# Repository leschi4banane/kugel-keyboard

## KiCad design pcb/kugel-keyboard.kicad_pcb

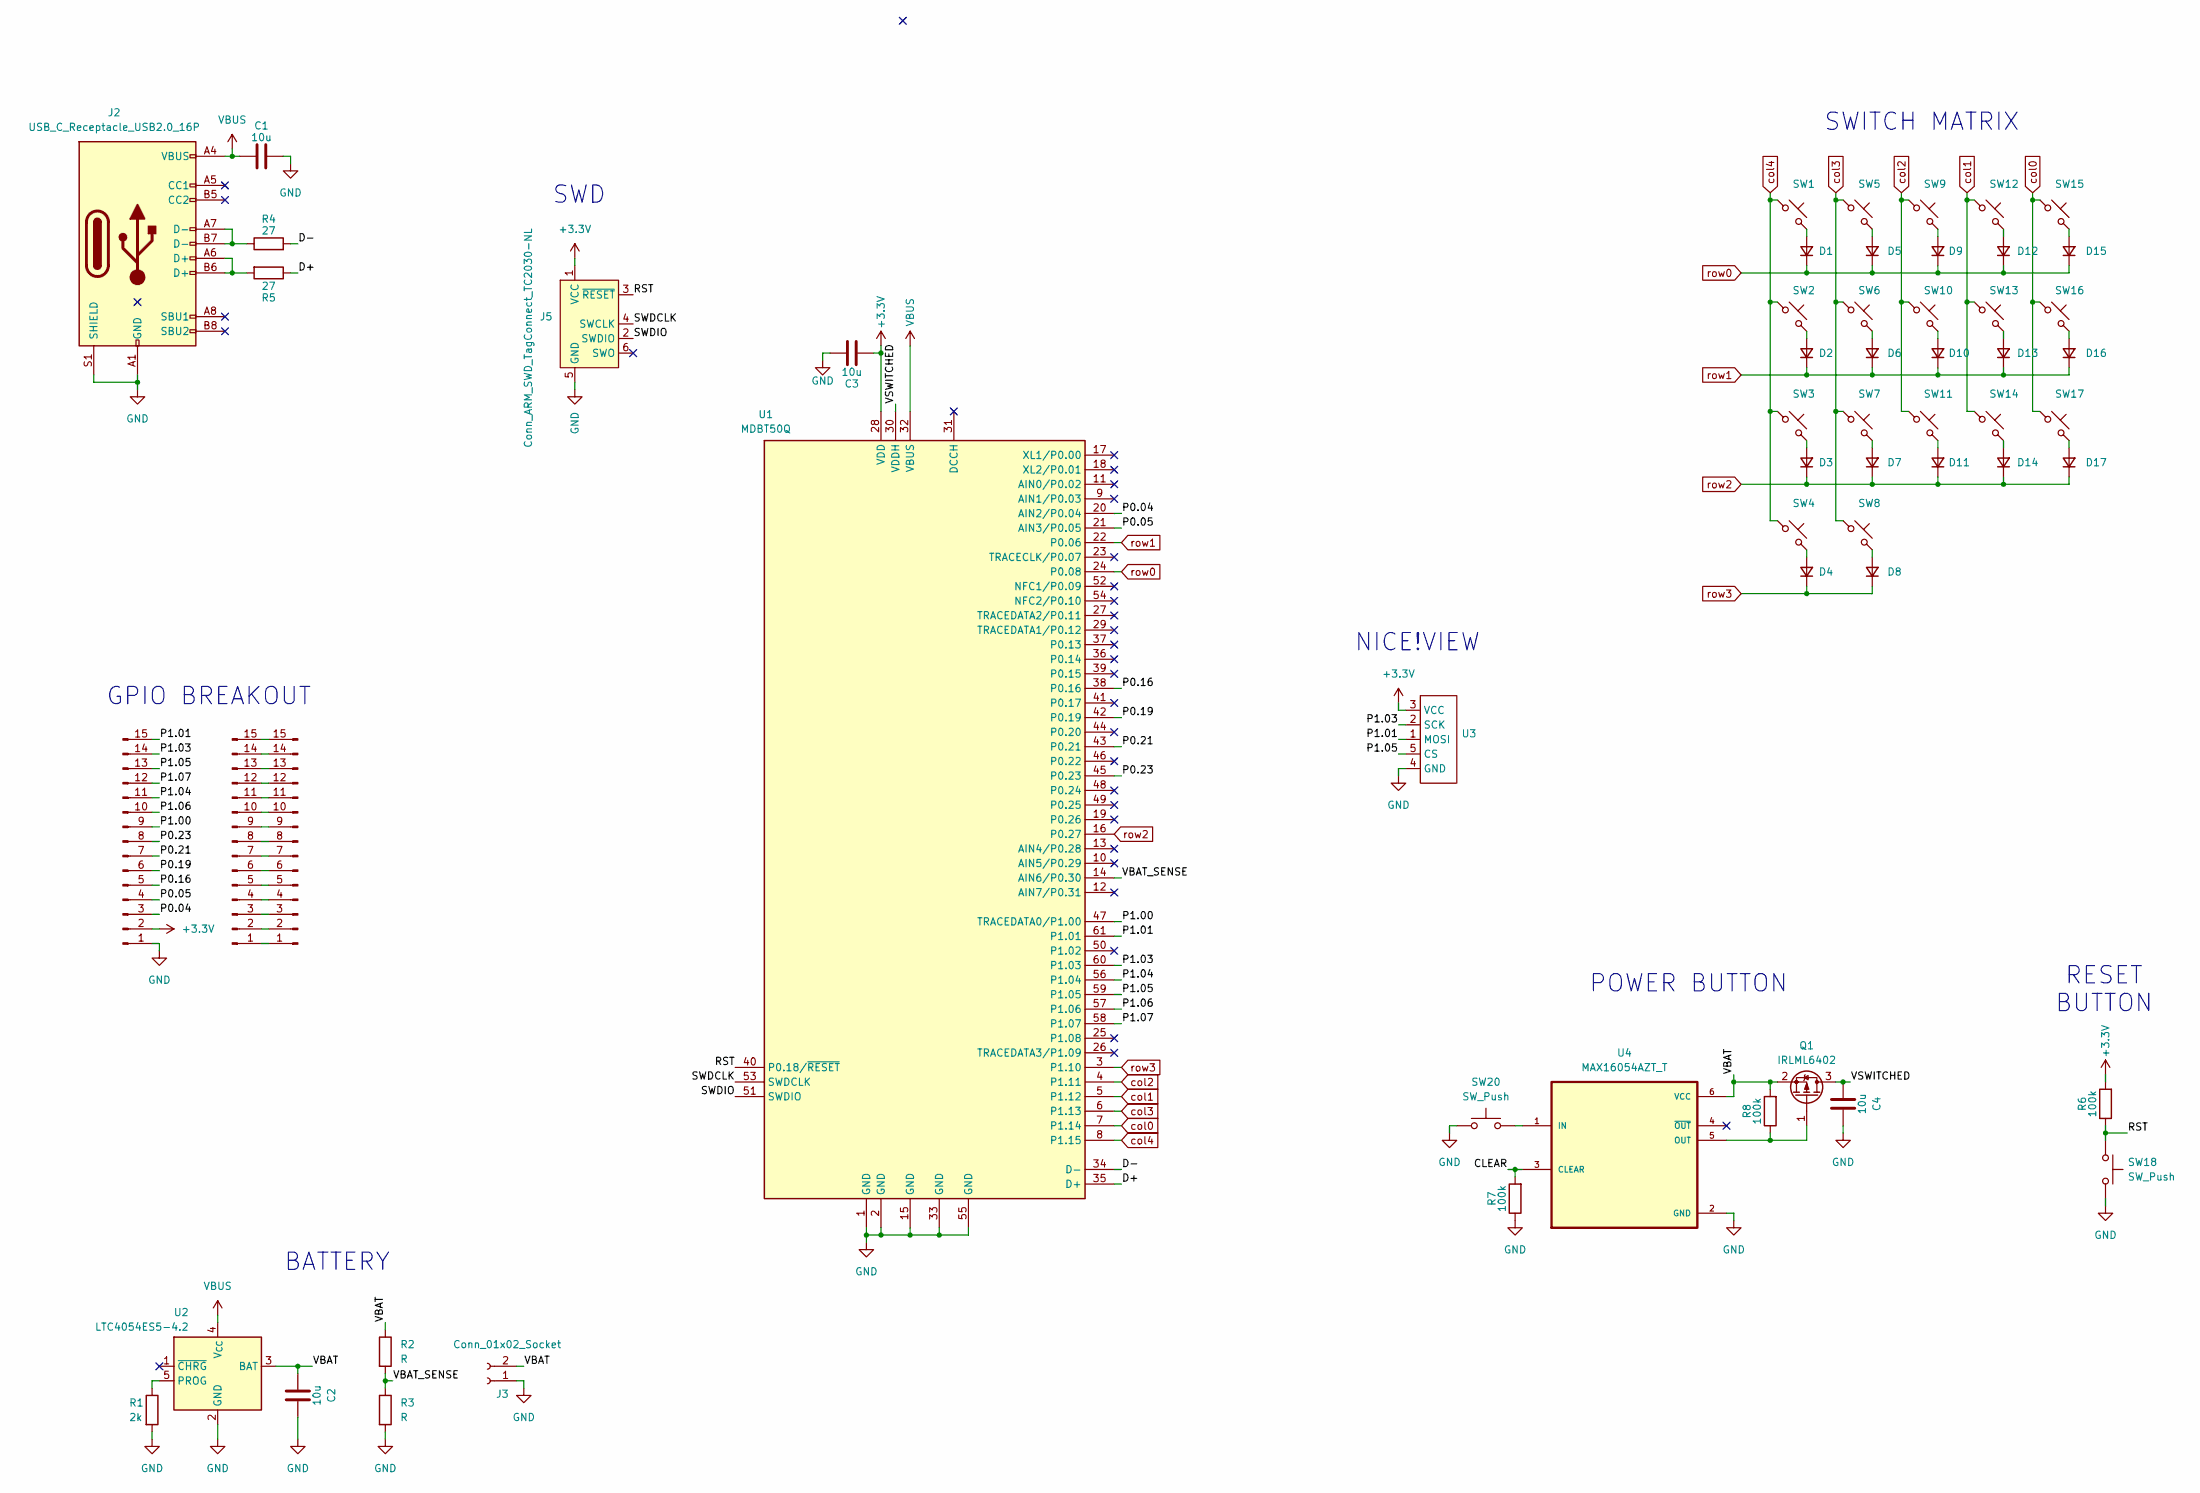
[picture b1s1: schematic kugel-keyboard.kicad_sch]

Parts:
C1, C2, C3, C4: 10u; C_0603_1608Metric_Pad1.08x0.95mm_HandSolder
D1, D2, D3, D4, D5, D6, D7, D8, D9, D10, D11, D12, D13, D14, D15, D16, D17: D_Small; Nexperia_CFP3_SOD-123W
J1, J6: Conn_01x15_Pin; Hirose_FH12-15S-0.5SH_1x15-1MP_P0.50mm_Horizontal
J2: USB_C_Receptacle_USB2.0_16P; USB_C_Receptacle_GCT_USB4105-xx-A_16P_TopMnt_Horizontal
J3: Conn_01x02_Socket; Battery_solder_pads
J4: Conn_01x15_Pin; PinHeader_1x15_P2.54mm_Vertical
J5: Conn_ARM_SWD_TagConnect_TC2030-NL; Tag-Connect_TC2030-IDC-NL_2x03_P1.27mm_Vertical
Q1: IRLML6402; SOT-23
R1: 2k; R_0603_1608Metric_Pad0.98x0.95mm_HandSolder
R2, R3: R; R_0603_1608Metric_Pad0.98x0.95mm_HandSolder
R4, R5: 27; R_0603_1608Metric_Pad0.98x0.95mm_HandSolder
R6, R7, R8: 100k; R_0603_1608Metric_Pad0.98x0.95mm_HandSolder
SW1, SW2, SW3, SW4, SW5, SW6, SW7, SW8, SW9, SW10, SW11, SW12, SW13, SW14, SW15, SW16, SW17: MX_SW_HS; Kailh_socket_PG1350
SW18, SW20: SW_Push; SW_TL6340AF160Q
U1: MDBT50Q; MDBT50Q-1MV2
U2: LTC4054ES5-4.2; TSOT-23-5
U3: nice!view
U4: MAX16054AZT_T; SOT95P275X110-6N

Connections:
+3.3V: C3.1, J5.1 (VCC), J6.2, R6.2, U1.28 (VDD), U3.3 (VCC)
/CLEAR: R7.2, U4.3 (CLEAR)
/D+: R5.1, U1.35 (D+)
/D-: R4.2, U1.34 (D-)
/P0.04: J6.3, U1.20 (AIN2/P0.04)
/P0.05: J6.4, U1.21 (AIN3/P0.05)
/P0.16: J6.5, U1.38 (P0.16)
/P0.19: J6.6, U1.42 (P0.19)
/P0.21: J6.7, U1.43 (P0.21)
/P0.23: J6.8, U1.45 (P0.23)
/P1.00: J6.9, U1.47 (TRACEDATA0/P1.00)
/P1.01: J6.15, U1.61 (P1.01), U3.1 (MOSI)
/P1.03: J6.14, U1.60 (P1.03), U3.2 (SCK)
/P1.04: J6.11, U1.56 (P1.04)
/P1.05: J6.13, U1.59 (P1.05), U3.5 (CS)
/P1.06: J6.10, U1.57 (P1.06)
/P1.07: J6.12, U1.58 (P1.07)
/RST: J5.3 (~RESET), R6.1, SW18.1, U1.40 (P0.18/~RESET)
/SWDCLK: J5.4 (SWCLK), U1.53 (SWDCLK)
/SWDIO: J5.2 (SWDIO), U1.51 (SWDIO)
/VBAT: C2.1, J3.2, Q1.2 (S), R2.1, R8.2, U2.3 (BAT), U4.6 (VCC)
/VBAT_SENSE: R2.2, R3.1, U1.14 (AIN6/P0.30)
/VSWITCHED: C4.1, Q1.3 (D), U1.30 (VDDH)
GND: C1.2, C2.2, C3.2, C4.2, J2.A1 (GND), J2.A12 (GND), J2.B1 (GND), J2.B12 (GND), J2.S1 (SHIELD), J3.1, J5.5 (GND), J6.1, J6.MP, R1.2, R3.2, R7.1, SW18.2, SW20.1, U1.1 (GND), U1.2 (GND), U1.15 (GND), U1.33 (GND), U1.55 (GND), U2.2 (GND), U3.4 (GND), U4.2 (GND)
unnamed: D1.2 (A), SW1.2
unnamed: D2.2 (A), SW2.2
unnamed: D3.2 (A), SW3.2
unnamed: D4.2 (A), SW4.2
unnamed: D5.2 (A), SW5.2
unnamed: D6.2 (A), SW6.2
unnamed: D7.2 (A), SW7.2
unnamed: D8.2 (A), SW8.2
unnamed: D9.2 (A), SW9.2
unnamed: D10.2 (A), SW10.2
unnamed: D11.2 (A), SW11.2
unnamed: D12.2 (A), SW12.2
unnamed: D13.2 (A), SW13.2
unnamed: D14.2 (A), SW14.2
unnamed: D15.2 (A), SW15.2
unnamed: D16.2 (A), SW16.2
unnamed: D17.2 (A), SW17.2
unnamed: J1.1, J4.1
unnamed: J1.2, J4.2
unnamed: J1.3, J4.3
unnamed: J1.4, J4.4
unnamed: J1.5, J4.5
unnamed: J1.6, J4.6
unnamed: J1.7, J4.7
unnamed: J1.8, J4.8
unnamed: J1.9, J4.9
unnamed: J1.10, J4.10
unnamed: J1.11, J4.11
unnamed: J1.12, J4.12
unnamed: J1.13, J4.13
unnamed: J1.14, J4.14
unnamed: J1.15, J4.15
unnamed: J2.A6 (D+), J2.B6 (D+), R5.2
unnamed: J2.A7 (D-), J2.B7 (D-), R4.1
unnamed: Q1.1 (G), R8.1, U4.5 (OUT)
unnamed: R1.1, U2.5 (PROG)
unnamed: SW20.2, U4.1 (IN)
VBUS: C1.1, J2.A4 (VBUS), J2.A9 (VBUS), J2.B4 (VBUS), J2.B9 (VBUS), U1.32 (VBUS), U2.4 (V_{CC})
col0: SW15.1, SW16.1, SW17.1, U1.7 (P1.14)
col1: SW12.1, SW13.1, SW14.1, U1.5 (P1.12)
col2: SW9.1, SW10.1, SW11.1, U1.4 (P1.11)
col3: SW5.1, SW6.1, SW7.1, SW8.1, U1.6 (P1.13)
col4: SW1.1, SW2.1, SW3.1, SW4.1, U1.8 (P1.15)
row0: D1.1 (K), D5.1 (K), D9.1 (K), D12.1 (K), D15.1 (K), U1.24 (P0.08)
row1: D2.1 (K), D6.1 (K), D10.1 (K), D13.1 (K), D16.1 (K), U1.22 (P0.06)
row2: D3.1 (K), D7.1 (K), D11.1 (K), D14.1 (K), D17.1 (K), U1.16 (P0.27)
row3: D4.1 (K), D8.1 (K), U1.3 (P1.10)

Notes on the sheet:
RESET BUTTON
GPIO BREAKOUT
NICE!VIEW
POWER BUTTON
SWITCH MATRIX
SWD
BATTERY

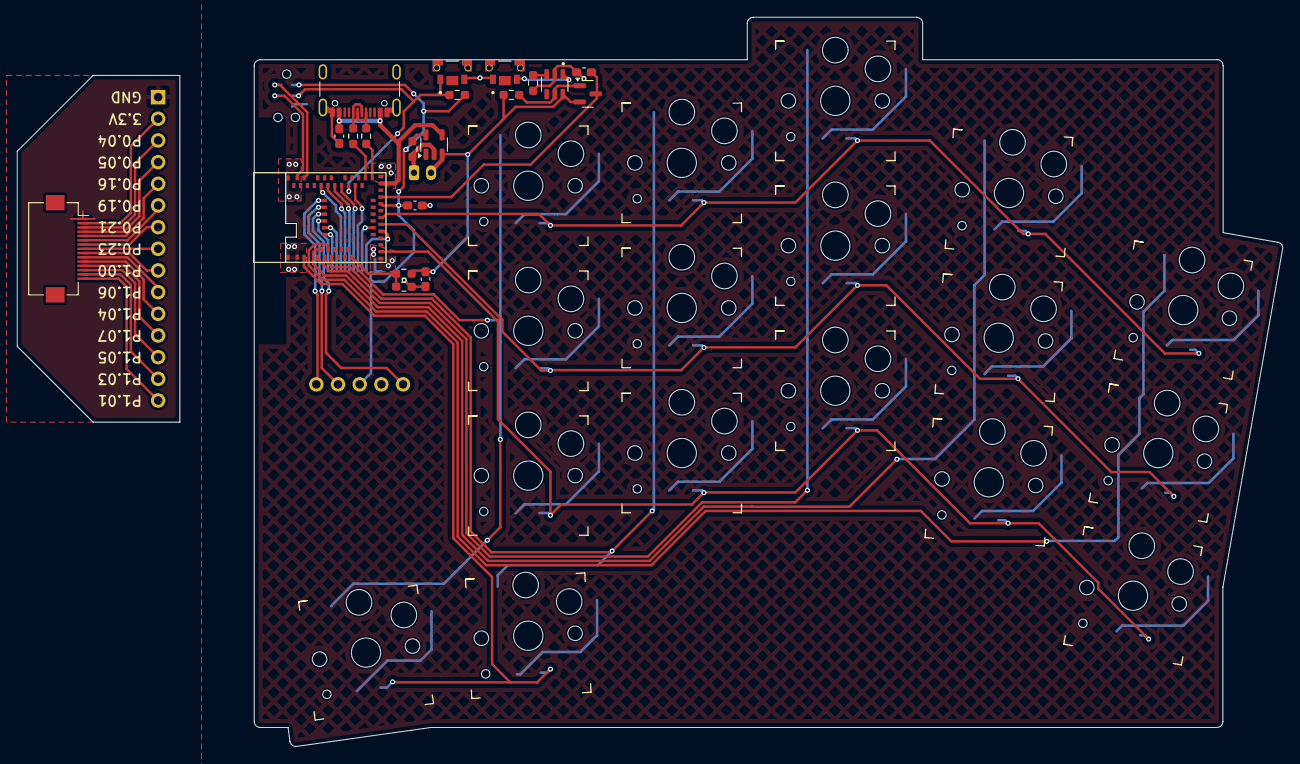
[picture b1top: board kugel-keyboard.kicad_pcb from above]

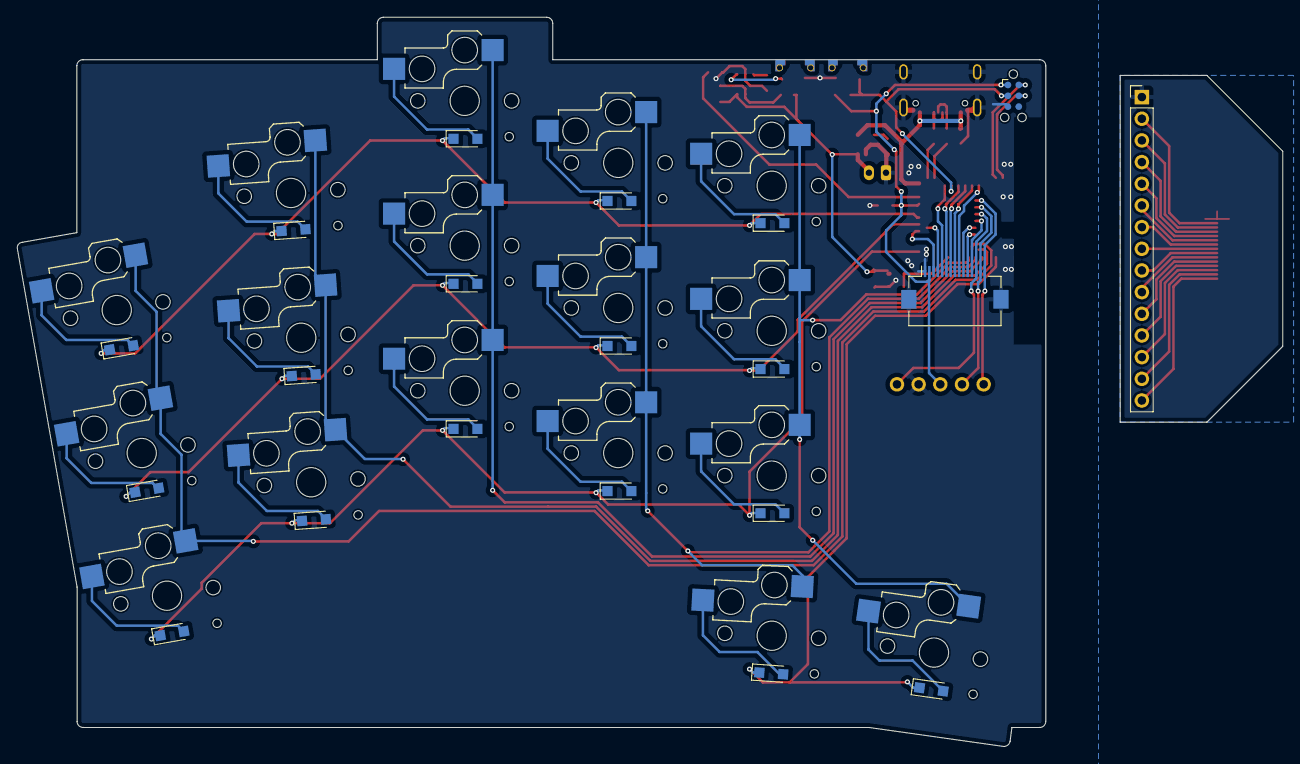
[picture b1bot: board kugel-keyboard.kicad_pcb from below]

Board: 2 copper layers, 148.3 x 85.5 mm, 59 parts (20 on the bottom side), 71 nets.

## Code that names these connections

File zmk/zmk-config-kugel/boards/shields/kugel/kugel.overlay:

#include <dt-bindings/zmk/matrix_transform.h>
#include <zephyr/dt-bindings/input/input-event-codes.h>
#include <input/processors.dtsi>
#include <dt-bindings/zmk/input_transform.h>
#include <dt-bindings/zmk/bt.h>
#include <dt-bindings/zmk/mouse.h>
#include <dt-bindings/zmk/outputs.h>
#include <behaviors/mouse_keys.dtsi>
#include <dt-bindings/zmk/ext_power.h>

&pinctrl {
    spi0_default: spi0_default {
        group1 {
            psels = <NRF_PSEL(SPIM_SCK, 1, 3)>,
                <NRF_PSEL(SPIM_MOSI, 1, 1)>,
                <NRF_PSEL(SPIM_MISO, 1, 1)>;
        };
    };

    spi0_sleep: spi0_sleep {
        group1 {
            psels = <NRF_PSEL(SPIM_SCK, 1, 3)>,
                <NRF_PSEL(SPIM_MOSI, 1, 1)>,
                <NRF_PSEL(SPIM_MISO, 1, 1)>;
            low-power-enable;
        };
    };
};

nice_view_spi: &spi0 {
    compatible = "nordic,nrf-spim";
    pinctrl-0 = <&spi0_default>;
    pinctrl-1 = <&spi0_sleep>;
    pinctrl-names = "default", "sleep";
    cs-gpios = <&gpio1 5 GPIO_ACTIVE_HIGH>;
};

/ {
    chosen {
        zmk,kscan = &default_kscan;
        zmk,matrix-transform = &default_transform;
        zmk,battery = &vbatt;
    };

    vbatt: vbatt {
        //compatible = "zmk,battery-voltage-divider";
        //io-channels = <&adc 6>;
        //output-ohms = <2000000>;
        //full-ohms = <2806000>;
        compatible = "zmk,battery-nrf-vddh";
    };

    default_kscan: kscan {
        compatible = "zmk,kscan-gpio-matrix";
        wakeup-source;
        diode-direction = "col2row";

        row-gpios = <&gpio0 4 (GPIO_ACTIVE_HIGH | GPIO_PULL_DOWN)>,   // row0
                    <&gpio0 6 (GPIO_ACTIVE_HIGH | GPIO_PULL_DOWN)>,   // row1
                    <&gpio0 8 (GPIO_ACTIVE_HIGH | GPIO_PULL_DOWN)>,   // row2
                    <&gpio0 20 (GPIO_ACTIVE_HIGH | GPIO_PULL_DOWN)>;  // row3

        col-gpios = <&gpio0 13 GPIO_ACTIVE_HIGH>, // col0
                    <&gpio0 15 GPIO_ACTIVE_HIGH>, // col1
                    <&gpio0 17 GPIO_ACTIVE_HIGH>, // col2
                    <&gpio0 19 GPIO_ACTIVE_HIGH>, // col3
                    <&gpio0 21 GPIO_ACTIVE_HIGH>; // col4
    };

    default_transform: matrix_transform {
        compatible = "zmk,matrix-transform";

        rows = <4>;
        columns = <5>;

        map = <
            RC(0,4) RC(0,3) RC(0,2) RC(0,1) RC(0,0)
            RC(1,4) RC(1,3) RC(1,2) RC(1,1) RC(1,0)
            RC(2,4) RC(2,3) RC(2,2) RC(2,1) RC(2,0)
                                    RC(3,1) RC(3,0)
        >;
    };
};

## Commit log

2025-02-25 added reference materials
2025-02-25 added a test config that can be compiled with to a 4 key test keyboard on our devboard
2025-02-25 added physical key positions
2025-02-25 added zmk folder and start of custom zmk modules
2025-02-25 added TODO list
2025-02-25 removed and ignored kicad backups
2025-02-25 removed github workflow, because it will be built locally
2025-02-25 moved led-test module to sperate git repo
2025-02-25 replaced zephyr module with zmk module
2025-02-25 fixed zmk modules submodule
2025-02-25 submodule change
2025-02-25 removed submodule
2025-02-25 made the submodules work again
2025-02-25 added correct submodule
2025-03-04 added right side PCB and GPIO breakout PCB
2025-03-11 added left side PCB and GPIO breakout PCB
2025-03-18 added ESD-protection
2025-03-18 edited nrfTest config
2025-03-18 added external oszilator
2025-03-18 replaced charge circuit for cost reasons
2025-03-19 replaced button ic and updated bom
2025-05-20 added kugel config and trackball and trackpad to nrfTest config
2025-05-27 added config for left side only
